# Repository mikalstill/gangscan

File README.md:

Introduction
============

Gang Scan is a simple attendance tracking system built for Scouts ACT's
Canberra Gang Show. It uses custom RFID badge reader devices based on
Raspberry Pis to track badge read events, which are streamed to a server.
Each badge reader is configured to either be an "in" or and "out" reader, and
therefore attendance can be calculated. The badge readers will queue scan
events and stream them to the server later if connectivity is intermittent.

Structure
=========

The structure of this repository is:

* deploy: deployment scripts.
* eagle: PCB layouts for the gang scan hardware.
* gangscan: the software stack for the badge readers.
* gangserver: the server side of the application.
* idcards: is a simple ID card art generation script with sample data. See the README in that directory for more detail.
* vendor: git sub-modules for dependancies.

Installation: Common Steps
==========================

First off, flash the latest raspberry pi debian to an SD card. You can find
it at https://www.raspberrypi.org/downloads/raspbian/ . I have been using the
Debian Stretch Lite image for development. I use Balena Etcher to flash the
SD cards, and this process is well documented elsewhere.

Insert this SD card into your raspberry pi and boot it. You'll need to have
the raspberry pi plugged into a HDMI monitor and USB keyboard and mouse for
the next steps.

* Log in: username is "pi" and password is "raspberry".
* Change the password: "passwd".
* Configure the pi:
  * `sudo raspi-config`
  * Join wifi (network options)
  * Enable ssh (interfacing options)
  * Expand filesystem (advanced options)
  * Reboot
* Update the operating system:
  * `sudo apt-get update`
  * `sudo apt-get dist-upgrade`
* Install ansible:
  * `sudo apt-get install python3-pip`
  * `sudo pip3 install ansible`
* Install git and vim, then clone gangscan:
  * `sudo apt-get install git vim`
  * `git clone https://github.com/mikalstill/gangscan`
  * `cd gangscan`
  * `git submodule update --init --recursive`

Installation: Gang Server
=========================

The gangserver advertises itself using a homegrown UDP protocol. It is assumed that
the server will be running on raspberry pi running debian (called raspbian).
This can be one of the gangscan devices if that is desirable for your
deployment. First follow the common installation steps above, once those
steps are done we have enough of a system to be able to do the rest of the
install via ansible plays.

Run ansible to install gangserver:

~~~~
$ /usr/local/bin/ansible-playbook -i hosts deploy/gangserver.yml
~~~~

This should install all the required software for the gangserver, and start
it on port 80. The server advertises itself on the network using avahi /
zeroconf networking, so you don't need to have the server running on a
machine with a known IP. However, knowing the IP of the server is very
useful for viewing reports, so perhaps put it on a static IP anyway.

Installation: Gang Scan
=======================

The RFID reader hardware runs a program called gangscan. To install it,
follow the common installation steps above, and then install gangscan with
ansible:

~~~~
$ /usr/local/bin/ansible-playbook -i hosts deploy/gangscan.yml
~~~~

Because the ansible changes the boot configuration of the raspberry pi (it
turns on SPI and PWN audio), you need to reboot before the scanner will work
correctly:

~~~~
$ sudo reboot
~~~~

Checking the status of Gang Scan
================================

Because Gang Scan uses systemd, you can check the status of the various
components using systemd commands. To see the general status of the server,
do this:

~~~~
$ sudo systemctl status gangserver
~~~~

To see recent log messages from the server, do this:

~~~~
$ sudo journalctl -u gangserver
~~~~

Hardware helpers
================

Gang Scan devices use an identity EEPROM to make sure the software is talking
to the right version of the hardware. To program EEPROMs, install the
developer software with Ansible like this:

~~~~
$ /usr/local/bin/ansible-playbook -i hosts deploy/eeprom_writer.yml
~~~~

Now we can program some EEPROMs. You'll need to build a little programming
circuit (see the notes below), and then run this tool:

~~~~
$ cd /home/pi/hats/eepromutils
$ sudo sh eepflash.sh -w -f=/home/pi/gangscan/eeprom/eeprom_settings.eep \
  -t=24c256 -d=1
~~~~

For more details about Raspberry Pi HAT EEPROMs, see my notes at
https://www.madebymikal.com/raspberry-pi-hat-identity-eeproms-a-simple-guide/

Credits
=======

Various parts of Gang Scan draw on previous Open Source or Creative Commons
artifacts:

* Material Design Icons are from https://cdn.materialdesignicons.com/3.5.95/.
** This includes the TTF Font, as well as account.png
* BebaseNeue is licensed under the creative commons and is from https://fontlibrary.org/en/font/bebas
* blip.wav is "Robot Blip" by Marianne Gagnon from http://soundbible.com/1682-Robot-Blip.html which is released under a CC Attribution 3.0 license.

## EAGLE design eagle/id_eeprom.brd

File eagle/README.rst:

Board notes:

* v0.1: the first board to be fabbed. Has LCD and RFID on different SPI buses.
* ... (incremental tweaking including better track sizing, and nicer labels)
* v0.6: the second board to be fabbed. Has LCD and RFID on different SPI buses, and prototype
  audio support. Unfortunately, SPI1 conflicts with the audio hardware and the RFID reader
  needs to be moved onto SPI0 for this to work correctly.
* v0.7: tweaked footprint labels to be more accurate. Moved RFID reader onto SPIO bus to free
  up pins for audio. Corrected MKT capacitor pitch to 5mm.
* v0.8: correct resistor pitch (RCL_0207/7); connect RFID IRQ line to Raspberry Pi for
  later use (reduce CPU load for RFID reads by avoiding polling); moved LiPo socket down a
  little so the JST connector fits more naturally into a case; added an i2c EEPROM to
  comply with the HAT specification.

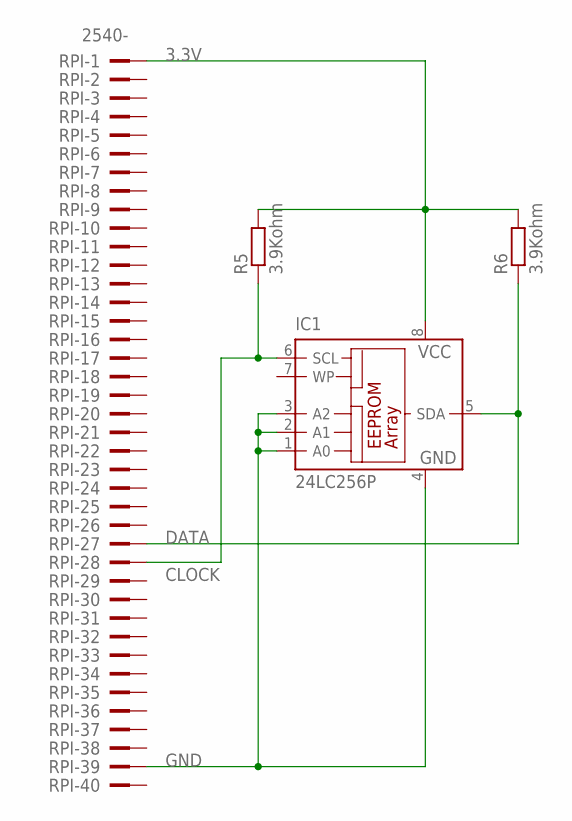
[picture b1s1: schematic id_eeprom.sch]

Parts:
IC1: 24LC256P; DIL8
R5, R6: 3.9Kohm; 0207/7
RPI: 2540-; PAK100/2500-40

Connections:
3.3V: IC1.8 (VCC), R5.2, R6.2, RPI.1
CLOCK: IC1.6 (SCL), R5.1, RPI.28
DATA: IC1.5 (SDA), R6.1, RPI.27
GND: IC1.1 (A0), IC1.2 (A1), IC1.3 (A2), IC1.4 (GND), RPI.39

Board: 2 copper layers, 4 parts (0 on the bottom side), 4 nets, no tracks yet.

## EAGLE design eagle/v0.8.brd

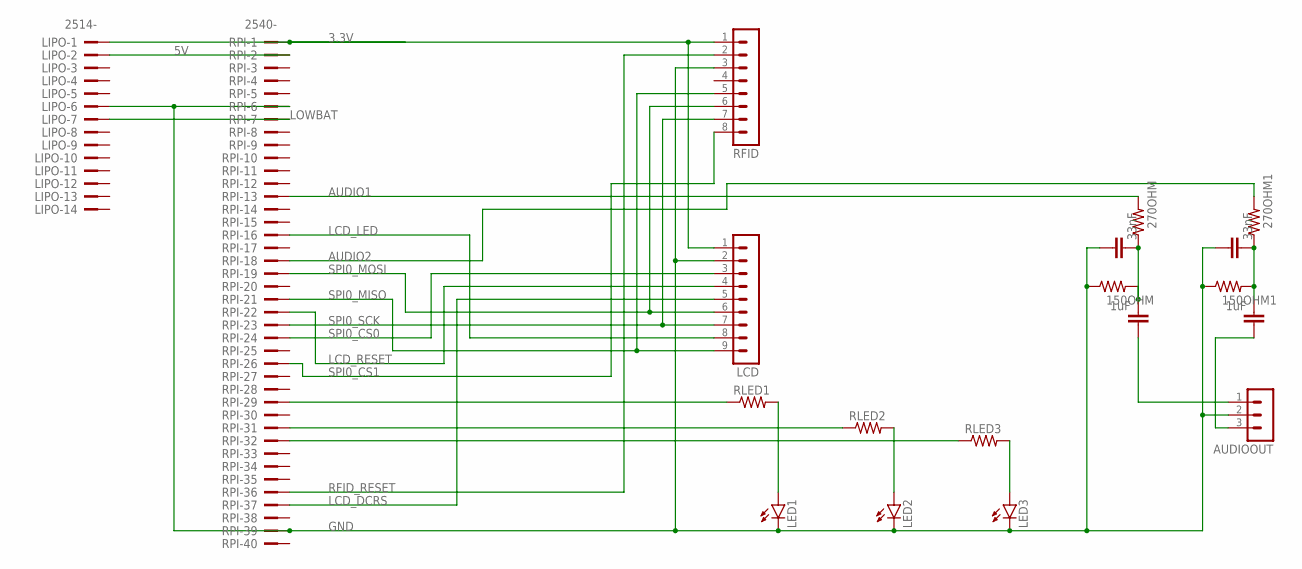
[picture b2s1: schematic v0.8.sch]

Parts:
150OHM, 150OHM1, 270OHM, 270OHM1: R-US_0204/5; 0204/5
AUDIOOUT: MA03-1
C1, C2: 33nF; C5B5
E1, E2: 1uF; C025-025X050
LCD: MA09-1
LED1, LED2, LED3: LED3MM
LIPO: 2514-; PAK100/2500-14
RFID: MA08-1
RLED1, RLED2, RLED3: R-US_0204/5; 0204/5
RPI: 2540-; PAK100/2500-40

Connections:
3.3V: LCD.1, LIPO.1, RFID.1, RPI.1
5V: LIPO.2, RPI.2
AUDIO1: 270OHM.2, RPI.13
AUDIO2: 270OHM1.2, RPI.18
GND: 150OHM.1, 150OHM1.1, AUDIOOUT.2, C1.1, C2.1, LCD.2, LED1.K (C), LED2.K (C), LED3.K (C), LIPO.6, RFID.3, RPI.6, RPI.39
LCD_DCRS: LCD.5, RPI.37
LCD_LED: LCD.8, RPI.16
LCD_RESET: LCD.4, RPI.22
LOWBAT: LIPO.7, RPI.7
unnamed: 150OHM.2, 270OHM.1, C1.2, E1.2
unnamed: LED2.A, RLED2.2
unnamed: LED3.A, RLED3.2
unnamed: RLED1.1, RPI.29
unnamed: RLED2.1, RPI.31
unnamed: RLED3.1, RPI.32
unnamed: 150OHM1.2, 270OHM1.1, C2.2, E2.2
unnamed: AUDIOOUT.1, E1.1
unnamed: AUDIOOUT.3, E2.1
unnamed: LED1.A, RLED1.2
RFID_RESET: RFID.2, RPI.36
SPI0_CS0: LCD.3, RPI.24
SPI0_CS1: RFID.8, RPI.26
SPI0_MISO: LCD.9, RFID.5, RPI.21
SPI0_MOSI: LCD.6, RFID.6, RPI.19
SPI0_SCK: LCD.7, RFID.7, RPI.23

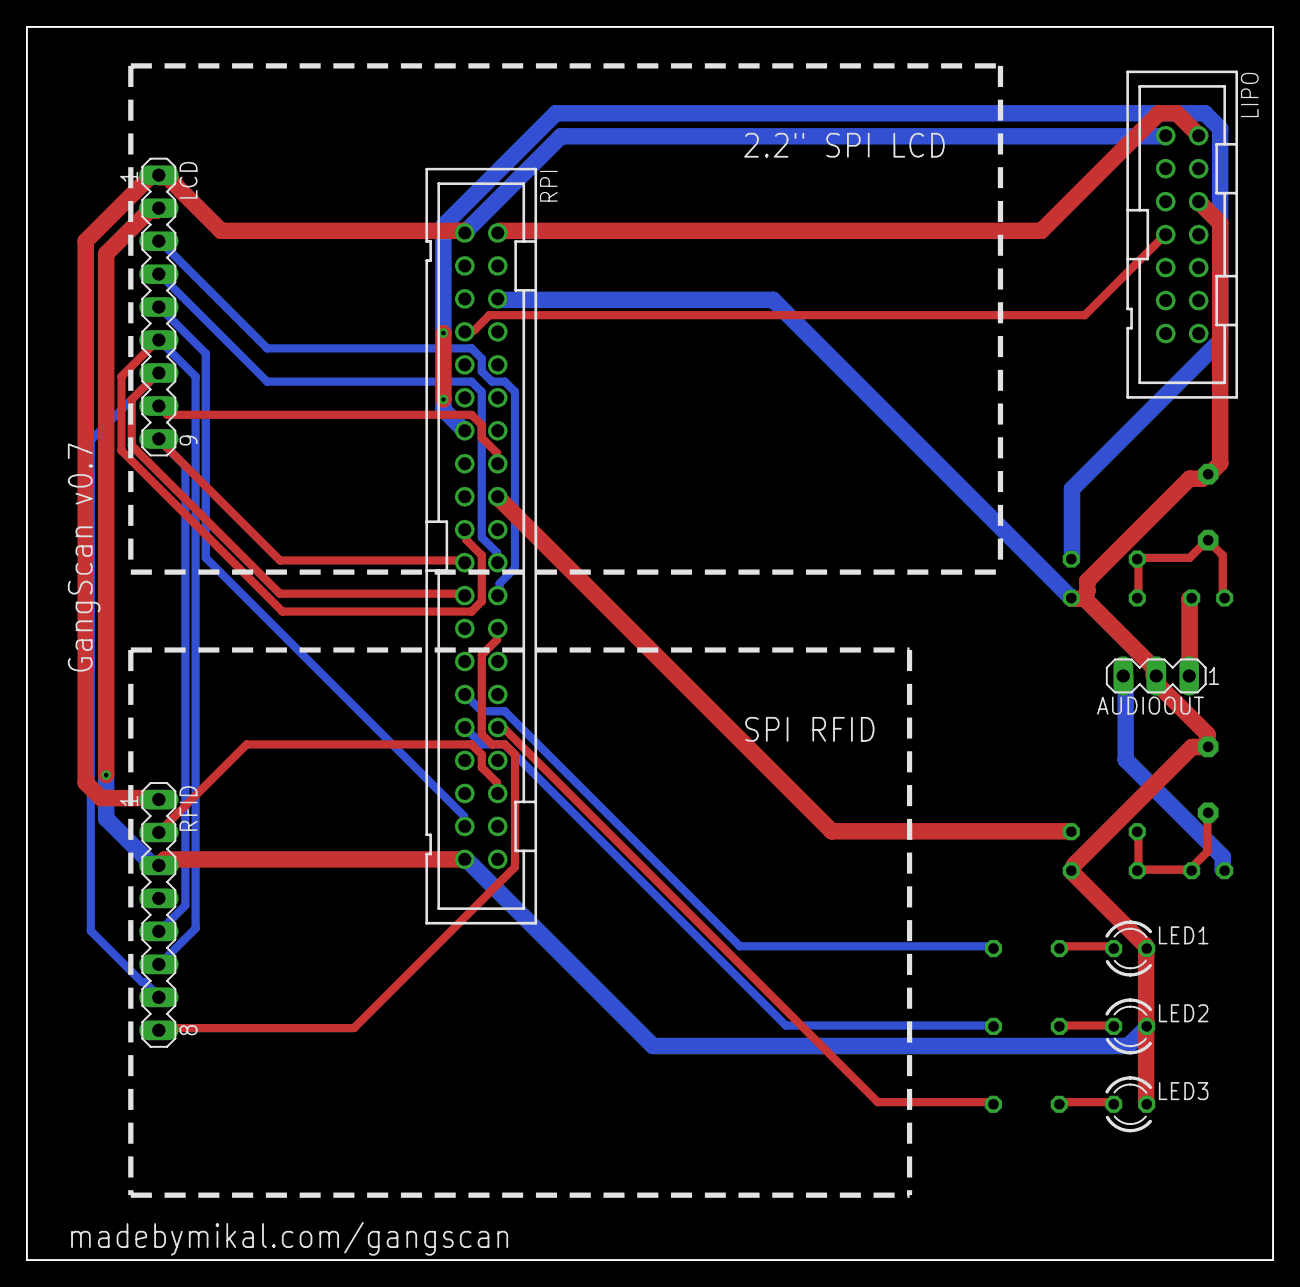
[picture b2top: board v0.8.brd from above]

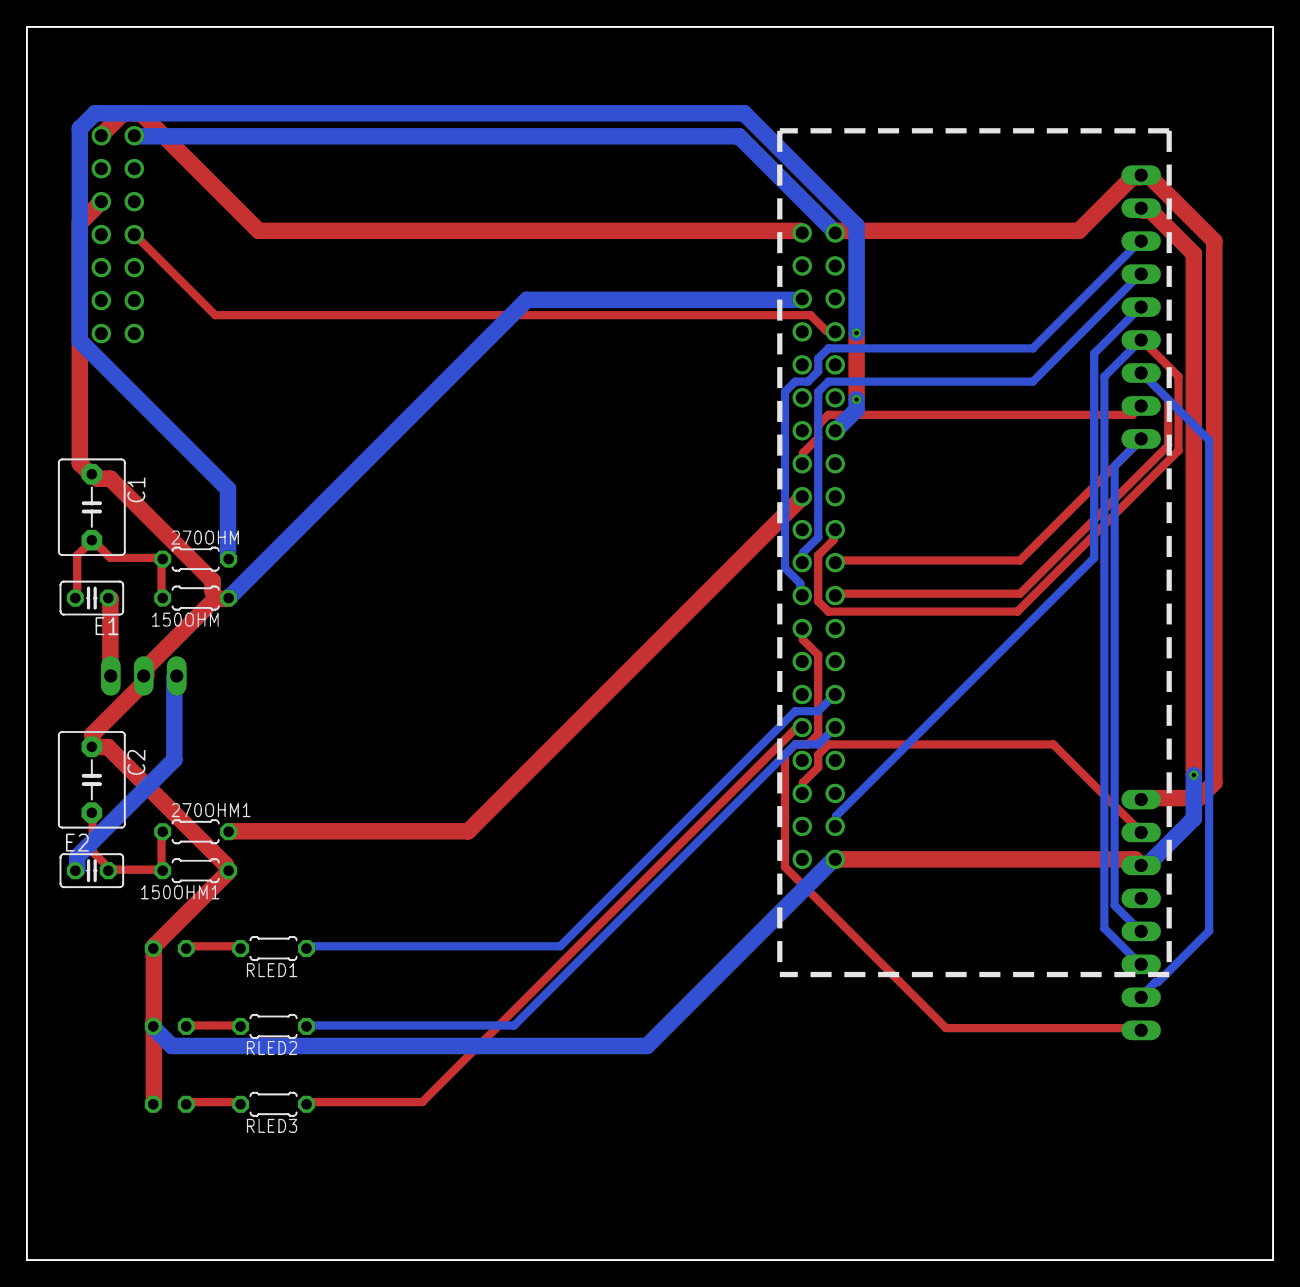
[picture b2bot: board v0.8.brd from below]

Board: 2 copper layers, 96.0 x 95.0 mm, 19 parts (11 on the bottom side), 25 nets.

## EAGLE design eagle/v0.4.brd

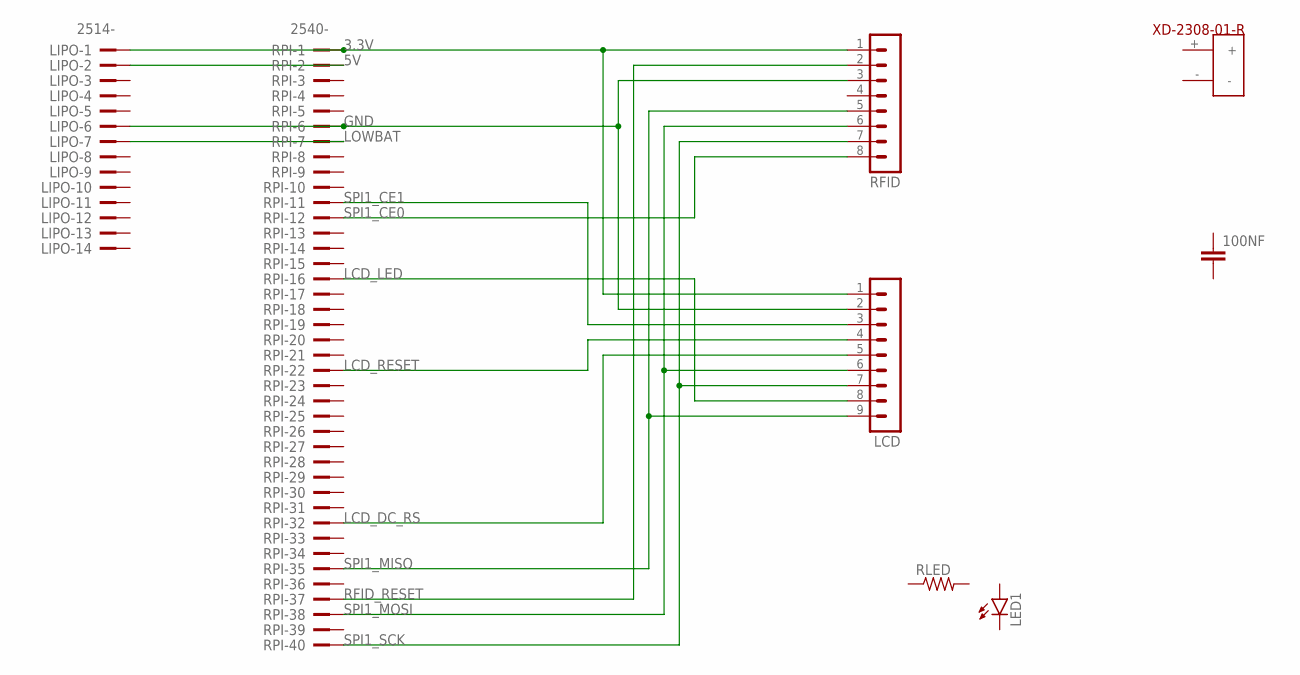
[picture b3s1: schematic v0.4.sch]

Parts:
100NF: C-EU025-025X050; C025-025X050
LCD: MA09-1
LED1: LED3MM
LIPO: 2514-; PAK100/2500-14
RFID: MA08-1
RLED: R-US_0204/5; 0204/5
RPI: 2540-; PAK100/2500-40
U$1: XD-2308-01-R

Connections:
3.3V: LCD.1, LIPO.1, RFID.1, RPI.1
5V: LIPO.2, RPI.2
GND: LCD.2, LIPO.6, RFID.3, RPI.6
LCD_DC_RS: LCD.5, RPI.32
LCD_LED: LCD.8, RPI.16
LCD_RESET: LCD.4, RPI.22
LOWBAT: LIPO.7, RPI.7
RFID_RESET: RFID.2, RPI.37
SPI1_CE0: RFID.8, RPI.12
SPI1_CE1: LCD.3, RPI.11
SPI1_MISO: LCD.9, RFID.5, RPI.35
SPI1_MOSI: LCD.6, RFID.6, RPI.38
SPI1_SCK: LCD.7, RFID.7, RPI.40

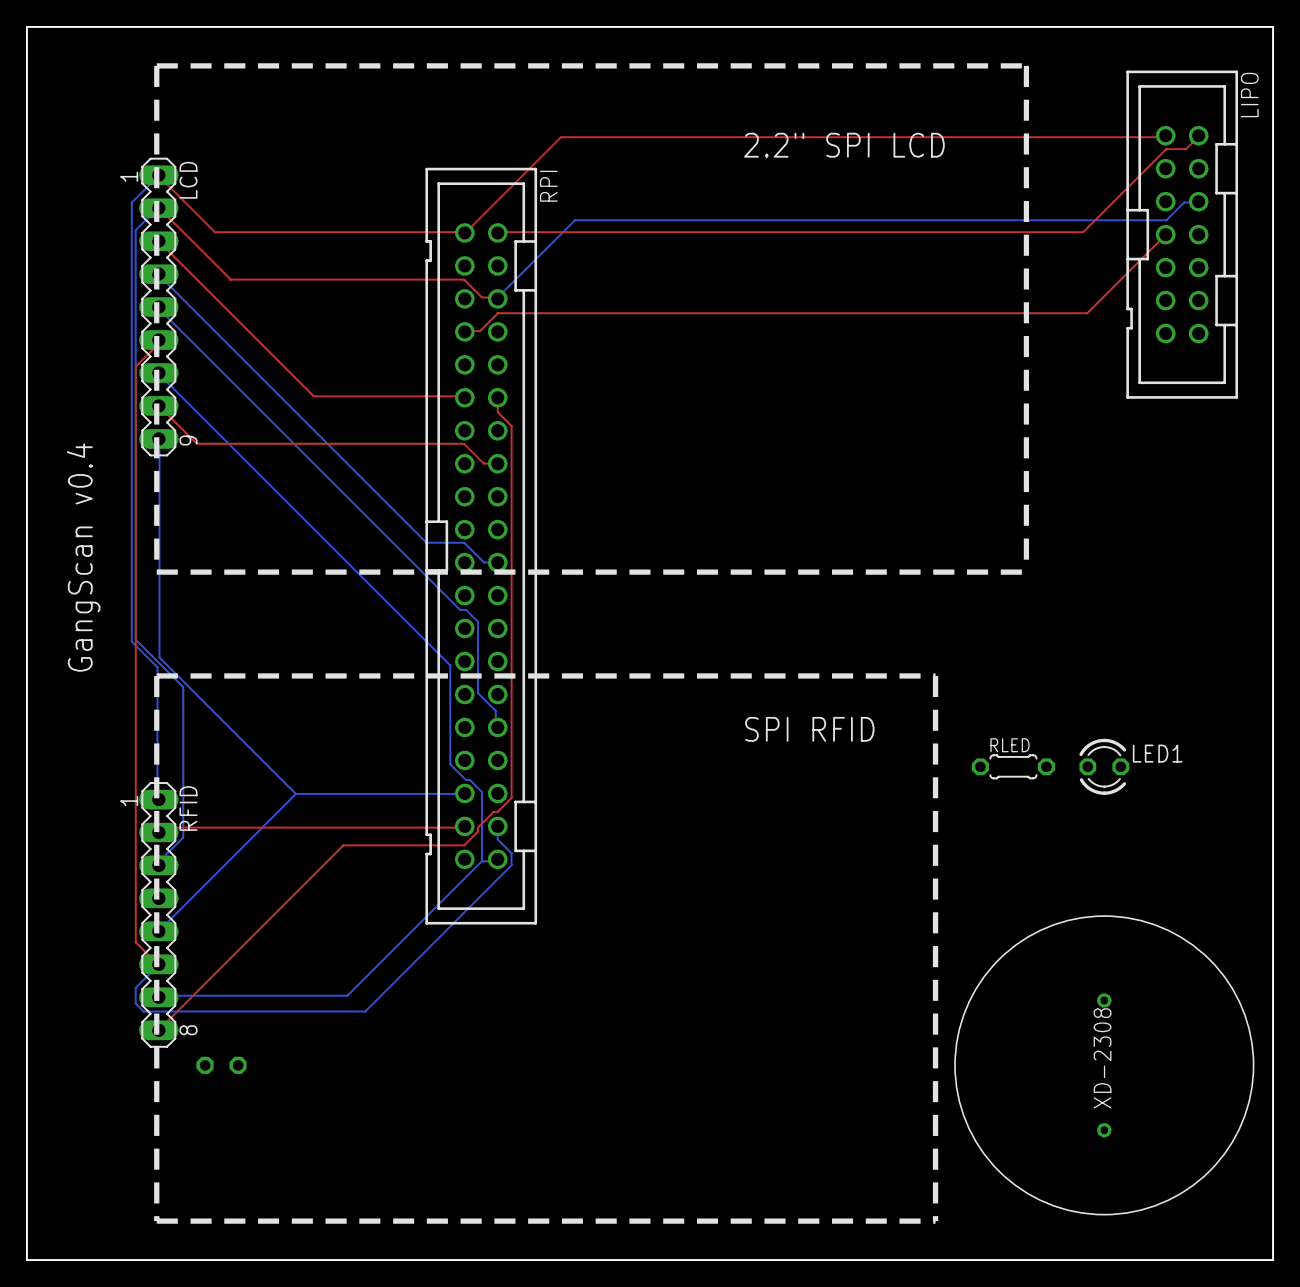
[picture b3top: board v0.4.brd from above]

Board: 2 copper layers, 96.0 x 95.0 mm, 8 parts (1 on the bottom side), 13 nets.

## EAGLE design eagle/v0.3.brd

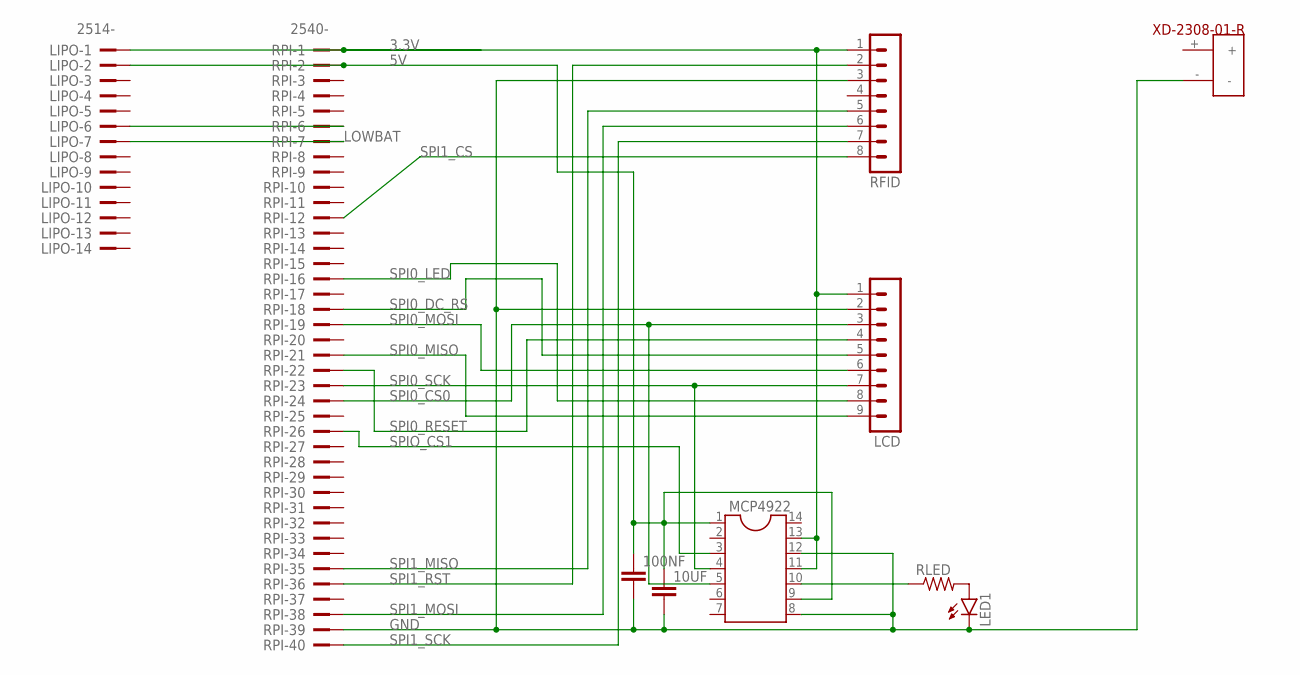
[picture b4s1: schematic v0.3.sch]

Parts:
10UF, 100NF: C-EU025-025X050; C025-025X050
LCD: MA09-1
LED1: LED3MM
LIPO: 2514-; PAK100/2500-14
MCP4922: DIL14
RFID: MA08-1
RLED: R-US_0204/5; 0204/5
RPI: 2540-; PAK100/2500-40
U$1: XD-2308-01-R

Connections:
3.3V: LCD.1, LIPO.1, MCP4922.11, MCP4922.13, RFID.1, RPI.1
5V: 10UF.1, 100NF.1, LIPO.2, MCP4922.1, MCP4922.9, RPI.2
GND: 10UF.2, 100NF.2, LCD.2, LED1.K (C), MCP4922.8, MCP4922.12, RFID.3, RPI.39, U$1.-
LOWBAT: LIPO.7, RPI.7
unnamed: LIPO.6, RPI.6
unnamed: MCP4922.10, RLED.1
unnamed: LED1.A, RLED.2
SPI0_CS0: LCD.3, MCP4922.5, RPI.24
SPI0_DC_RS: LCD.5, RPI.18
SPI0_LED: LCD.8, RPI.16
SPI0_MISO: LCD.9, RPI.21
SPI0_MOSI: LCD.6, RPI.19
SPI0_RESET: LCD.4, RPI.22
SPI0_SCK: LCD.7, MCP4922.4, RPI.23
SPI1_CS: RFID.8, RPI.12
SPI1_MISO: RFID.5, RPI.35
SPI1_MOSI: RFID.6, RPI.38
SPI1_RST: RFID.2, RPI.36
SPI1_SCK: RFID.7, RPI.40
SPIO_CS1: MCP4922.3, RPI.26

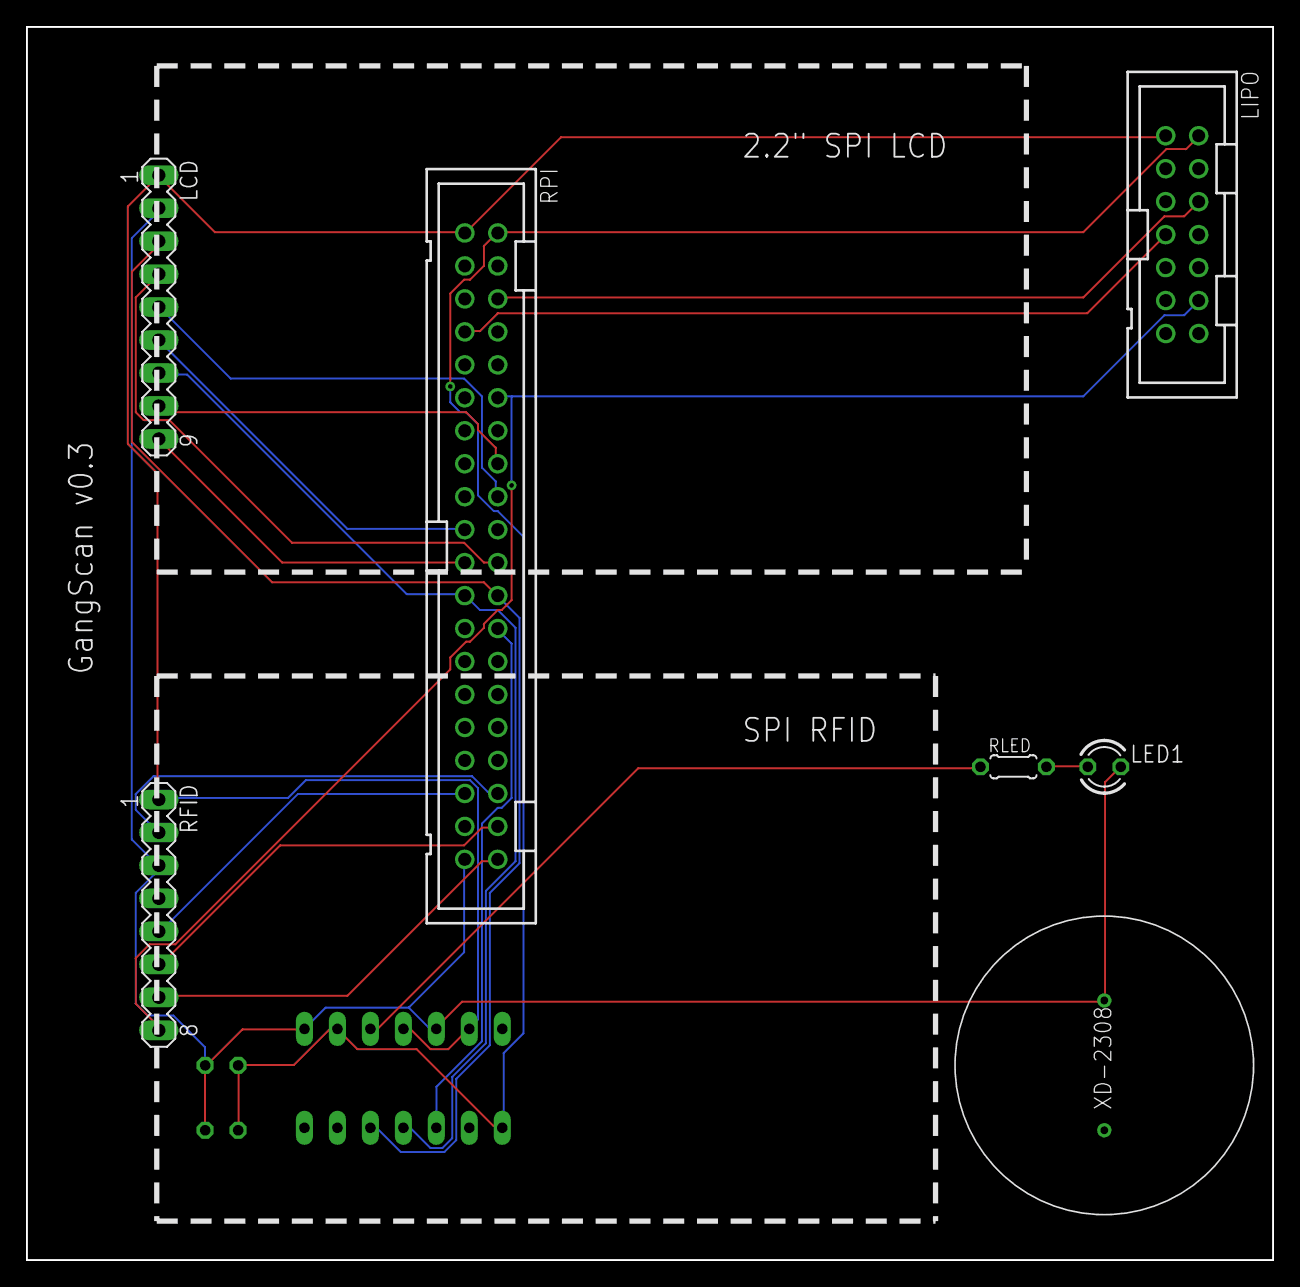
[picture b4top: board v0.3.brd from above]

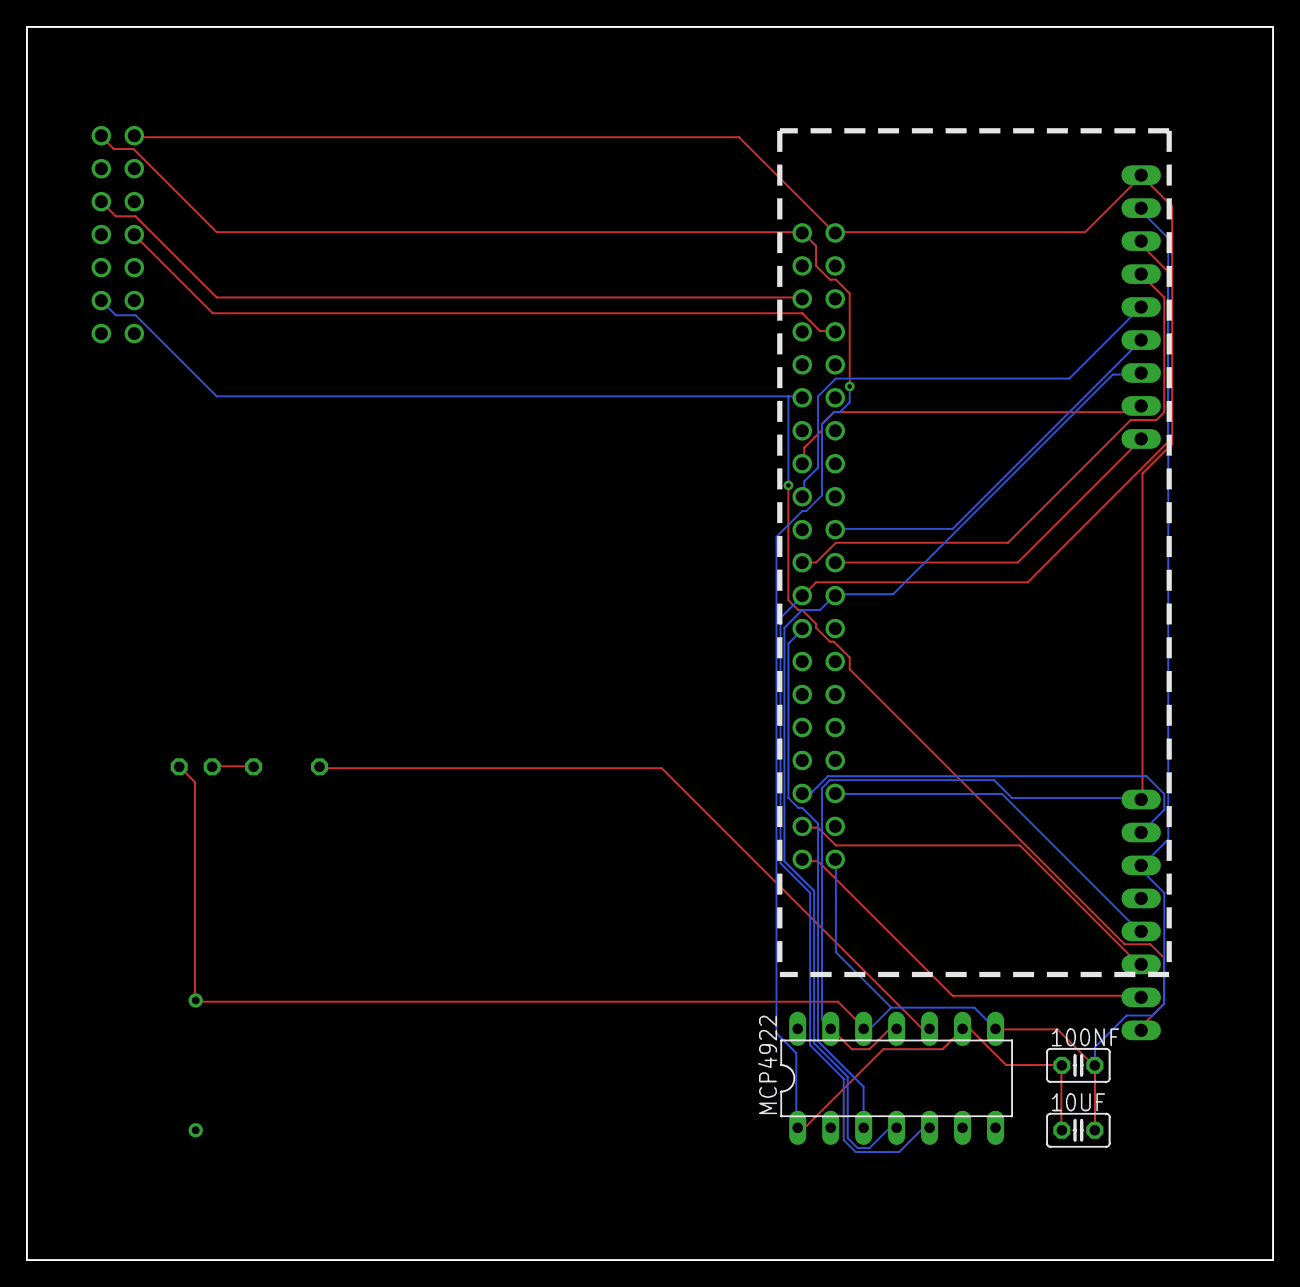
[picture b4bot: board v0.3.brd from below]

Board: 2 copper layers, 96.0 x 95.0 mm, 10 parts (3 on the bottom side), 20 nets.

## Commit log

2019-03-23 Initial commit, just hacking.
2019-03-23 A simple status screen now works.
2019-03-23 More work on the status screen.
2019-03-23 Fighting RFID on the second SPI bus.
2019-03-24 Writing and reading cards with hashes.
2019-03-24 RFID and display now work.
2019-03-24 Discovering that image_to_data() is the slow part of display.
2019-03-24 Significant performance improvements to screen update.
2019-03-24 Display working nicely.
2019-03-26 Get scanner working with simple retry queueing.
2019-04-03 Eagle design for 0.1 PCB
2019-04-05 Starting to think about the next version of the PCB.
2019-04-09 More work on the PCB.
2019-04-09 v0.3 board
2019-04-09 Library for the PCB speaker
2019-04-09 Tweaks to reporting
2019-04-09 Make the vendor'ed code more obvious for now
2019-04-09 Do submodules more rightlier
2019-04-09 Add blip.wav
2019-04-11 First attempts at playing a WAV file.
2019-04-11 Correct lipo connections.
2019-04-12 First attempt at moving everything to SPI1 so we can do PWM audio.
2019-04-12 We don't need to rearrange the SPI buses.
    I was wrong, partially because I didn't realize that my labelling
    of SPI pins was ambigious. The signal that was sitting on a PWM pin
    _isn't_ part of the SPI bus, its just a GPIO signal that I can
    move to another pin. This frees up the pins I need for PWM audio
    without requiring a wholesale rearrangement of the PCB design.
    So let's do that instead. I've called it board version 0.5...
2019-04-15 Change pin for LCD to make space for PWM audio and add missing file.
2019-04-15 Remove no longer needed file
2019-04-28 Add raspi boot configuration file.
2019-05-10 Let's do another run of boards, this time with more LEDs and sound half done.
2019-05-20 Working on the v0.7 board.
2019-05-20 Move RFID to SPI0 to free up pins for audio (board v0.7).
2019-05-21 Board version v0.7
2019-05-28 Add ability to serve local static files.
2019-05-28 Add a .gitignore file
2019-05-28 Start working on install docs.
2019-05-28 Fix markup.
2019-05-28 Document and automate installation of the server.
2019-05-29 Installation for gangscan and py3 fixups.
2019-05-29 config.txt stuff is now handled by ansible
2019-05-30 Tweak install docs.
2019-05-30 Fixups from testing on a production v0.7 board.
2019-05-30 Cleanup requirement for config files with multiple readers.
2019-05-30 Correct argparse code.
2019-05-30 Refactor and move scanner config to being fed from server.
2019-05-30 Nicer logging, and streaming config from server to client.
2019-05-30 Handle server being absent on boot.
2019-05-31 Handle connectivity checks better.
2019-05-31 Use health checks to update config.
2019-05-31 Fix missing variable
2019-05-31 Dynamically regenerate location icon.
2019-05-31 Fix typo in config file path.
2019-06-04 Start thinking about a v0.8 board.
2019-06-06 Working on gain control.
2019-06-06 Add simple ID card generation script with sample data.
2019-06-06 Changes to support gang show 2018.
2019-06-09 Update how we write cards.
2019-06-09 Write new cards, and import the status database.
2019-06-09 Move runtime data store out of the git directory.
2019-06-10 Updated report to handle more than two locations, fixed card hashing.
2019-06-21 Changes to make the UI snappier.
2019-06-21 First attempt at IRQ driven card reading.
2019-06-21 v0.8 board
2019-06-22 Rewrite read_rfid to use a more reliable RFID library.
2019-06-22 Update ansible to install the new RFID library.
2019-06-22 Better logging.
2019-06-22 Better logging of exceptions in badge data parsing.
2019-06-22 Fix double encoding bug.
2019-06-22 Ignore stray error codes from the RFID library.
2019-06-22 Indicate to users card read errors.
2019-06-22 Continued UI tweaks.
2019-06-22 Make the rfid reader less chatty.
2019-06-23 Check hardware version on start.
2019-06-23 Move to a more reliable service discovery mechanism.
    Avahi / zeroconf / mDNS wasn't being reliable. Over time lookups
    would get slower and slower and eventually consume all available CPU
    on the gangscan host. Instead, use a simple broadcast UDP mechanism
    to advertise the existence of a server, and go from there.
2019-06-23 Other icons.
2019-07-01 Safety and reporting tweaks
2019-07-03 EEPROM configuration
2019-07-03 Add setup for EEPROM programming.
2019-07-03 Finish eeprom docs.
2019-07-04 Canberra 2019 deployment tweaks.
2019-07-06 Tweak gain.
2019-07-07 Import tweaks.
2019-07-07 Log events into a sqlite database.
2019-07-07 Event reporting UI.
2019-07-07 Filter event log by user.
2019-07-07 Expose event log UI in attendance report.
2019-07-08 Do a better job of caching client config.
2019-07-08 Bug fixes.
2019-07-08 Try to make the reader a bit more reliable.
2019-07-08 Decide what interface to query based on uname output.
2019-07-08 Make web classes (mostly) alphabetical.
2019-07-08 Pollute the global namespace less.
2019-07-08 Create a framework for user login.
2019-07-08 Require users to login to see web interface.
2019-07-08 Create framework for manual events.
2019-07-08 Add UI to manually edit person location.
2019-07-08 Simple UI to add new users.
2019-07-09 Add missing template file.
2019-07-09 Display more nicelier on a phone screen.
2019-07-09 Very early support for alternative groupings.
2019-07-09 added openscad and stl files for 3d printed cases
2019-07-09 Show cast patrols before support patrols.
2019-07-09 Link for virtual Amy.
2019-07-09 Remove debug log line.
2019-07-09 Fighting ordering.
2019-07-09 Sort patrol members.
2019-07-10 UI for badge creation.
2019-07-11 Debug tweaks for RFID readers.
2019-07-11 Make debug flag work right.
2019-07-11 Move to unbuffered IO to resolve old card reprocessing issues.
2020-03-08 Add a simple user creation helper.
2020-03-08 Fix patrol name bug.
